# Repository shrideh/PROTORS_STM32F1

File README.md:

# PROTORS_STM32F1
This is a repository of our **open-source board** based on the *STM32F103C8 microcontroller from STMicroelectronics*.

## Pinout and dimensions
For the available functions of every pin, we strongly encourage you to read the [microcontroller datasheet](https://www.st.com/resource/en/datasheet/stm32f103c8.pdf), or use `variant/variant.h` and `variant/PeripherialPins.c` files.

## Electronics
* Whole *KiCad project* is available in `PROTORS_STM32F1` folder.

## Requirements
[Arduino](https://www.arduino.cc/)<br>
[Arduino_Core_STM32](https://github.com/stm32duino/Arduino_Core_STM32)<br>

This board is tested with
**Arduino IDE 1.8.12** and **Arduino_Core_STM32 1.8.0**.

## Installation & Usage
To use this board within [Arduino IDE](https://www.arduino.cc/en/main/software) you need [STM32 core support for Arduino](https://github.com/stm32duino/Arduino_Core_STM32). Every new board is called *variant*, to add this variant to list, you first need to find out where are source files on your system (follow [Where are sources](https://github.com/stm32duino/wiki/wiki/Where-are-sources#stm32-core-sources-files-location) page).

* Create folder `PROTORS_STM32F1` in `variants` folder and copy all files from this repositories `variant` folder (`ldscript.ld`, `PeripheralPins.c`, `PinNamesVar.h`, `variant.cpp`, and `variant.h`).
* Append `boards_additional.txt` content to `boards.txt` file (it is in same folder as `variant` folder), to declare the new variant.
* Restart *Arduino IDE* and try your new board. From ***Tools/Board*** menu select `Generic STM32F1 series` then from ***Tools/Board part number*** select `PROTORS STM32F1`. Set all of the rest options and upload sketch using ***STM32CubeProgrammer (SWD)*** (ST-LINK/V2 programmer).
* It is possible to customize some core definitions or compiler options by adding a file named `build_opt.h` in the sketch directory (follow [Build options](https://github.com/stm32duino/wiki/wiki/Customize-build-options-using-build_opt.h) page)

## License
Copyright (C) 2020 PROTORS  <info@protors.co>

Licensed under CERN-OHL-P version 2

You may redistribute and modify this documentation and make products
using it under the terms of the [CERN-OHL-P v2](https://ohwr.org/project/cernohl/wikis/Documents/CERN-OHL-version-2).
This documentation is distributed WITHOUT ANY EXPRESS OR IMPLIED
WARRANTY, INCLUDING OF MERCHANTABILITY, SATISFACTORY QUALITY
AND FITNESS FOR A PARTICULAR PURPOSE. Please see the CERN-OHL-P v2
for applicable conditions.

For more information view [LICENSE.txt](./LICENSE.txt) file.

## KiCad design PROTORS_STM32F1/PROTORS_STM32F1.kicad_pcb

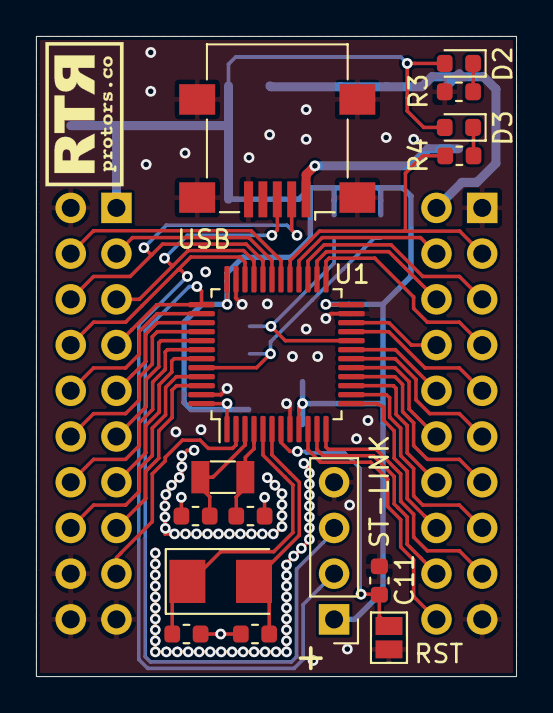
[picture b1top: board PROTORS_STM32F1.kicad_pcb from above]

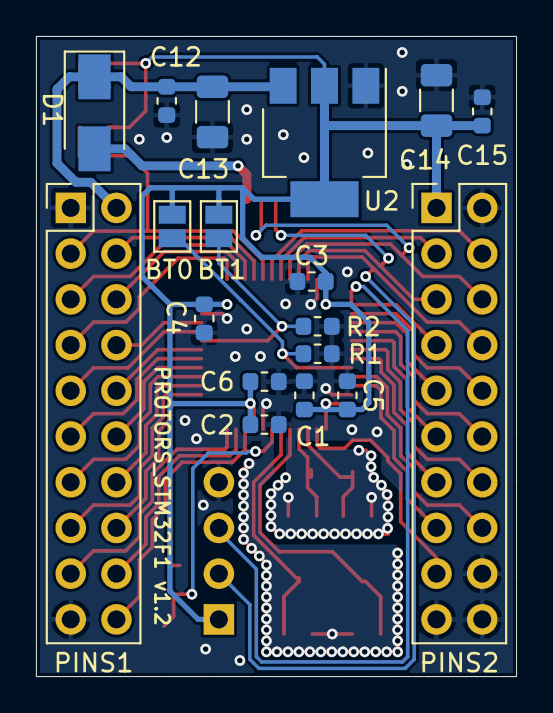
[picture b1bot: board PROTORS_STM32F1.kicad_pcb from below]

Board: 2 copper layers, 26.7 x 35.6 mm, 33 parts (18 on the bottom side), 45 nets.

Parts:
BT0: BOOT0; SolderJumper-2_P1.3mm_Open_Pad1.0x1.5mm
BT1: BOOT1; SolderJumper-2_P1.3mm_Open_Pad1.0x1.5mm
C1: 4.7uF; C_0603_1608Metric
C2: 1uF; C_0603_1608Metric
C3, C4, C5, C11, C12, C15: 100nF; C_0603_1608Metric
C6: 10nF; C_0603_1608Metric
C7, C8: 20pF; C_0603_1608Metric
C9, C10: 12pF; C_0603_1608Metric
C13, C14: 10uF; C_1206_3216Metric
D1: SS14; D_SMA
D2, D3: LED; LED_0603_1608Metric
PINS1: PINS_1; PinHeader_2x10_P2.54mm_Vertical
PINS2: PINS_2; PinHeader_2x10_P2.54mm_Vertical
R1, R2: 10k; R_0603_1608Metric
R3, R4: 1k; R_0603_1608Metric
RST: RESET; SolderJumper-2_P1.3mm_Open_Pad1.0x1.5mm
ST-LINK: ST-LINK; PinHeader_1x04_P2.54mm_Vertical
U1: STM32F103C8Tx; LQFP-48_7x7mm_P0.5mm
U2: AMS1117-3.3; SOT-223-3_TabPin2
USB: USB_B_Mini; USB_Mini-B_Lumberg_2486_01_Horizontal
Y1: 8MHz; Crystal_SMD_5032-2Pin_5.0x3.2mm
Y2: 32.768kHz; Crystal_SMD_3215-2Pin_3.2x1.5mm

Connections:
+3V3: BT0.2, BT1.2, C1.2, C2.2, C3.2, C4.2, C5.2, C6.2, C14.1, C15.1, D2.2, D3.2, PINS2.1, ST-LINK.1, U1.1, U1.9, U1.24, U1.36, U1.48, U2.2
+5V: C12.2, C13.1, D1.1, PINS1.2, U2.3
BOOT_0: BT0.1, R1.1, U1.44
GND: C1.1, C2.1, C3.1, C4.1, C5.1, C6.1, C7.2, C8.2, C9.2, C10.2, C11.1, C12.1, C13.2, C14.2, C15.2, PINS1.1, PINS1.19, PINS2.2, PINS2.18, PINS2.19, PINS2.20, R1.2, R2.2, R3.1, RST.2, ST-LINK.4, U1.8, U1.23, U1.35, U1.47, U2.1, USB.5, USB.6
HSE_1: C7.1, U1.5, Y1.1
HSE_2: C8.1, U1.6, Y1.2
LSE_1: C9.1, U1.3, Y2.1
LSE_2: C10.1, U1.4, Y2.2
unnamed: D1.2, USB.1
unnamed: D2.1, R3.2
unnamed: D3.1, R4.2
PA_0: PINS1.20, U1.10
PA_1: PINS1.18, U1.11
PA_2: PINS1.17, U1.12
PA_3: PINS1.16, U1.13
PA_4: PINS1.15, U1.14
PA_5: PINS1.14, U1.15
PA_6: PINS1.13, U1.16
PA_7: PINS1.12, U1.17
PA_8: PINS1.3, R4.1, U1.29
PA_9: PINS2.4, U1.30
PA_10: PINS2.3, U1.31
PA_11: PINS2.6, U1.32, USB.2
PA_12: PINS2.5, U1.33, USB.3
PA_13: PINS2.8, ST-LINK.2, U1.34
PA_14: PINS2.7, ST-LINK.3, U1.37
PA_15: PINS2.10, U1.38
PB_0: PINS1.11, U1.18
PB_1: PINS1.10, U1.19
PB_2: BT1.1, R2.1, U1.20
PB_3: PINS2.9, U1.39
PB_4: PINS2.12, U1.40
PB_5: PINS2.11, U1.41
PB_6: PINS2.14, U1.42
PB_7: PINS2.13, U1.43
PB_8: PINS2.16, U1.45
PB_9: PINS2.15, U1.46
PB_10: PINS1.9, U1.21
PB_11: PINS1.8, U1.22
PB_12: PINS1.7, U1.25
PB_13: PINS1.6, U1.26
PB_14: PINS1.5, U1.27
PB_15: PINS1.4, U1.28
PC_13: PINS2.17, U1.2
RST: C11.2, RST.1, U1.7

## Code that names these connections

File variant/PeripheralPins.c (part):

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
#ifdef HAL_ADC_MODULE_ENABLED
WEAK const PinMap PinMap_ADC[] = {
  {PA_0,  ADC1,  STM_PIN_DATA_EXT(STM_MODE_ANALOG, GPIO_NOPULL, 0, 0, 0)}, // ADC1_IN0
  //  {PA_0,  ADC2,  STM_PIN_DATA_EXT(STM_MODE_ANALOG, GPIO_NOPULL, 0, 0, 0)}, // ADC2_IN0
  {PA_1,  ADC1,  STM_PIN_DATA_EXT(STM_MODE_ANALOG, GPIO_NOPULL, 0, 1, 0)}, // ADC1_IN1
  //  {PA_1,  ADC2,  STM_PIN_DATA_EXT(STM_MODE_ANALOG, GPIO_NOPULL, 0, 1, 0)}, // ADC2_IN1
  {PA_2,  ADC1,  STM_PIN_DATA_EXT(STM_MODE_ANALOG, GPIO_NOPULL, 0, 2, 0)}, // ADC1_IN2
  //  {PA_2,  ADC2,  STM_PIN_DATA_EXT(STM_MODE_ANALOG, GPIO_NOPULL, 0, 2, 0)}, // ADC2_IN2
  {PA_3,  ADC1,  STM_PIN_DATA_EXT(STM_MODE_ANALOG, GPIO_NOPULL, 0, 3, 0)}, // ADC1_IN3
  //  {PA_3,  ADC2,  STM_PIN_DATA_EXT(STM_MODE_ANALOG, GPIO_NOPULL, 0, 3, 0)}, // ADC2_IN3
  {PA_4,  ADC1,  STM_PIN_DATA_EXT(STM_MODE_ANALOG, GPIO_NOPULL, 0, 4, 0)}, // ADC1_IN4
  //  {PA_4,  ADC2,  STM_PIN_DATA_EXT(STM_MODE_ANALOG, GPIO_NOPULL, 0, 4, 0)}, // ADC2_IN4
  {PA_5,  ADC1,  STM_PIN_DATA_EXT(STM_MODE_ANALOG, GPIO_NOPULL, 0, 5, 0)}, // ADC1_IN5
  //  {PA_5,  ADC2,  STM_PIN_DATA_EXT(STM_MODE_ANALOG, GPIO_NOPULL, 0, 5, 0)}, // ADC2_IN5
  {PA_6,  ADC1,  STM_PIN_DATA_EXT(STM_MODE_ANALOG, GPIO_NOPULL, 0, 6, 0)}, // ADC1_IN6
  //  {PA_6,  ADC2,  STM_PIN_DATA_EXT(STM_MODE_ANALOG, GPIO_NOPULL, 0, 6, 0)}, // ADC2_IN6
  {PA_7,  ADC1,  STM_PIN_DATA_EXT(STM_MODE_ANALOG, GPIO_NOPULL, 0, 7, 0)}, // ADC1_IN7
  //  {PA_7,  ADC2,  STM_PIN_DATA_EXT(STM_MODE_ANALOG, GPIO_NOPULL, 0, 7, 0)}, // ADC2_IN7
  {PB_0,  ADC1,  STM_PIN_DATA_EXT(STM_MODE_ANALOG, GPIO_NOPULL, 0, 8, 0)}, // ADC1_IN8
  //  {PB_0,  ADC2,  STM_PIN_DATA_EXT(STM_MODE_ANALOG, GPIO_NOPULL, 0, 8, 0)}, // ADC2_IN8
  {PB_1,  ADC1,  STM_PIN_DATA_EXT(STM_MODE_ANALOG, GPIO_NOPULL, 0, 9, 0)}, // ADC1_IN9
  //  {PB_1,  ADC2,  STM_PIN_DATA_EXT(STM_MODE_ANALOG, GPIO_NOPULL, 0, 9, 0)}, // ADC2_IN9
  {NC,    NP,    0}
};
#endif
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
#ifdef HAL_I2C_MODULE_ENABLED
WEAK const PinMap PinMap_I2C_SDA[] = {
  {PB_7,  I2C1, STM_PIN_DATA(STM_MODE_AF_OD, GPIO_NOPULL, AFIO_NONE)},
  {PB_9,  I2C1, STM_PIN_DATA(STM_MODE_AF_OD, GPIO_NOPULL, AFIO_I2C1_ENABLE)},
#ifndef ARDUINO_BLUEPILL_F103C6
  {PB_11, I2C2, STM_PIN_DATA(STM_MODE_AF_OD, GPIO_NOPULL, AFIO_NONE)},
#endif
  {NC,    NP,    0}
};
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
#ifdef HAL_I2C_MODULE_ENABLED
WEAK const PinMap PinMap_I2C_SCL[] = {
  {PB_6,  I2C1, STM_PIN_DATA(STM_MODE_AF_OD, GPIO_NOPULL, AFIO_NONE)},
  {PB_8,  I2C1, STM_PIN_DATA(STM_MODE_AF_OD, GPIO_NOPULL, AFIO_I2C1_ENABLE)},
#ifndef ARDUINO_BLUEPILL_F103C6
  {PB_10, I2C2, STM_PIN_DATA(STM_MODE_AF_OD, GPIO_NOPULL, AFIO_NONE)},
#endif
  {NC,    NP,    0}
};
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
#ifdef HAL_TIM_MODULE_ENABLED
WEAK const PinMap PinMap_PWM[] = {
  {PA_0,  TIM2,   STM_PIN_DATA_EXT(STM_MODE_AF_PP, GPIO_PULLUP, AFIO_NONE, 1, 0)}, // TIM2_CH1
  //  {PA_0,  TIM2,   STM_PIN_DATA_EXT(STM_MODE_AF_PP, GPIO_PULLUP, AFIO_TIM2_PARTIAL_2, 1, 0)}, // TIM2_CH1
  {PA_1,  TIM2,   STM_PIN_DATA_EXT(STM_MODE_AF_PP, GPIO_PULLUP, AFIO_NONE, 2, 0)}, // TIM2_CH2
  //  {PA_1,  TIM2,   STM_PIN_DATA_EXT(STM_MODE_AF_PP, GPIO_PULLUP, AFIO_TIM2_PARTIAL_2, 2, 0)}, // TIM2_CH2
  {PA_2,  TIM2,   STM_PIN_DATA_EXT(STM_MODE_AF_PP, GPIO_PULLUP, AFIO_NONE, 3, 0)}, // TIM2_CH3
  //  {PA_2,  TIM2,   STM_PIN_DATA_EXT(STM_MODE_AF_PP, GPIO_PULLUP, AFIO_TIM2_PARTIAL_1, 3, 0)}, // TIM2_CH3
  {PA_3,  TIM2,   STM_PIN_DATA_EXT(STM_MODE_AF_PP, GPIO_PULLUP, AFIO_NONE, 4, 0)}, // TIM2_CH4
  //  {PA_3,  TIM2,   STM_PIN_DATA_EXT(STM_MODE_AF_PP, GPIO_PULLUP, AFIO_TIM2_PARTIAL_1, 4, 0)}, // TIM2_CH4
  {PA_6,  TIM3,   STM_PIN_DATA_EXT(STM_MODE_AF_PP, GPIO_PULLUP, AFIO_NONE, 1, 0)}, // TIM3_CH1
  //  {PA_7,  TIM1,   STM_PIN_DATA_EXT(STM_MODE_AF_PP, GPIO_PULLUP, AFIO_TIM1_PARTIAL, 1, 1)}, // TIM1_CH1N
  {PA_7,  TIM3,   STM_PIN_DATA_EXT(STM_MODE_AF_PP, GPIO_PULLUP, AFIO_NONE, 2, 0)}, // TIM3_CH2
  {PA_8,  TIM1,   STM_PIN_DATA_EXT(STM_MODE_AF_PP, GPIO_PULLUP, AFIO_NONE, 1, 0)}, // TIM1_CH1
  //  {PA_8,  TIM1,   STM_PIN_DATA_EXT(STM_MODE_AF_PP, GPIO_PULLUP, AFIO_TIM1_PARTIAL, 1, 0)}, // TIM1_CH1
  {PA_9,  TIM1,   STM_PIN_DATA_EXT(STM_MODE_AF_PP, GPIO_PULLUP, AFIO_NONE, 2, 0)}, // TIM1_CH2
  //  {PA_9,  TIM1,   STM_PIN_DATA_EXT(STM_MODE_AF_PP, GPIO_PULLUP, AFIO_TIM1_PARTIAL, 2, 0)}, // TIM1_CH2
  {PA_10, TIM1,   STM_PIN_DATA_EXT(STM_MODE_AF_PP, GPIO_PULLUP, AFIO_NONE, 3, 0)}, // TIM1_CH3
  //  {PA_10, TIM1,   STM_PIN_DATA_EXT(STM_MODE_AF_PP, GPIO_PULLUP, AFIO_TIM1_PARTIAL, 3, 0)}, // TIM1_CH3
  {PA_11, TIM1,   STM_PIN_DATA_EXT(STM_MODE_AF_PP, GPIO_PULLUP, AFIO_NONE, 4, 0)}, // TIM1_CH4
  //  {PA_11, TIM1,   STM_PIN_DATA_EXT(STM_MODE_AF_PP, GPIO_PULLUP, AFIO_TIM1_PARTIAL, 4, 0)}, // TIM1_CH4
  //  {PA_15, TIM2,   STM_PIN_DATA_EXT(STM_MODE_AF_PP, GPIO_PULLUP, AFIO_TIM2_PARTIAL_1, 1, 0)}, // TIM2_CH1
  {PA_15, TIM2,   STM_PIN_DATA_EXT(STM_MODE_AF_PP, GPIO_PULLUP, AFIO_TIM2_ENABLE, 1, 0)}, // TIM2_CH1
  //  {PB_0,  TIM1,   STM_PIN_DATA_EXT(STM_MODE_AF_PP, GPIO_PULLUP, AFIO_TIM1_PARTIAL, 2, 1)}, // TIM1_CH2N
  {PB_0,  TIM3,   STM_PIN_DATA_EXT(STM_MODE_AF_PP, GPIO_PULLUP, AFIO_NONE, 3, 0)}, // TIM3_CH3
  //  {PB_0,  TIM3,   STM_PIN_DATA_EXT(STM_MODE_AF_PP, GPIO_PULLUP, AFIO_TIM3_PARTIAL, 3, 0)}, // TIM3_CH3
  //  {PB_1,  TIM1,   STM_PIN_DATA_EXT(STM_MODE_AF_PP, GPIO_PULLUP, AFIO_TIM1_PARTIAL, 3, 1)}, // TIM1_CH3N
  {PB_1,  TIM3,   STM_PIN_DATA_EXT(STM_MODE_AF_PP, GPIO_PULLUP, AFIO_NONE, 4, 0)}, // TIM3_CH4
  //  {PB_1,  TIM3,   STM_PIN_DATA_EXT(STM_MODE_AF_PP, GPIO_PULLUP, AFIO_TIM3_PARTIAL, 4, 0)}, // TIM3_CH4
  //  {PB_3,  TIM2,   STM_PIN_DATA_EXT(STM_MODE_AF_PP, GPIO_PULLUP, AFIO_TIM2_PARTIAL_1, 2, 0)}, // TIM2_CH2
  {PB_3,  TIM2,   STM_PIN_DATA_EXT(STM_MODE_AF_PP, GPIO_PULLUP, AFIO_TIM2_ENABLE, 2, 0)}, // TIM2_CH2
  {PB_4,  TIM3,   STM_PIN_DATA_EXT(STM_MODE_AF_PP, GPIO_PULLUP, AFIO_TIM3_PARTIAL, 1, 0)}, // TIM3_CH1
  {PB_5,  TIM3,   STM_PIN_DATA_EXT(STM_MODE_AF_PP, GPIO_PULLUP, AFIO_TIM3_PARTIAL, 2, 0)}, // TIM3_CH2
#ifndef ARDUINO_BLUEPILL_F103C6
  {PB_6,  TIM4,   STM_PIN_DATA_EXT(STM_MODE_AF_PP, GPIO_PULLUP, AFIO_NONE, 1, 0)}, // TIM4_CH1
  {PB_7,  TIM4,   STM_PIN_DATA_EXT(STM_MODE_AF_PP, GPIO_PULLUP, AFIO_NONE, 2, 0)}, // TIM4_CH2
  {PB_8,  TIM4,   STM_PIN_DATA_EXT(STM_MODE_AF_PP, GPIO_PULLUP, AFIO_NONE, 3, 0)}, // TIM4_CH3
  {PB_9,  TIM4,   STM_PIN_DATA_EXT(STM_MODE_AF_PP, GPIO_PULLUP, AFIO_NONE, 4, 0)}, // TIM4_CH4
#endif
  //  {PB_10, TIM2,   STM_PIN_DATA_EXT(STM_MODE_AF_PP, GPIO_PULLUP, AFIO_TIM2_PARTIAL_2, 3, 0)}, // TIM2_CH3
  {PB_10, TIM2,   STM_PIN_DATA_EXT(STM_MODE_AF_PP, GPIO_PULLUP, AFIO_TIM2_ENABLE, 3, 0)}, // TIM2_CH3
  //  {PB_11, TIM2,   STM_PIN_DATA_EXT(STM_MODE_AF_PP, GPIO_PULLUP, AFIO_TIM2_PARTIAL_2, 4, 0)}, // TIM2_CH4
  {PB_11, TIM2,   STM_PIN_DATA_EXT(STM_MODE_AF_PP, GPIO_PULLUP, AFIO_TIM2_ENABLE, 4, 0)}, // TIM2_CH4
  {PB_13, TIM1,   STM_PIN_DATA_EXT(STM_MODE_AF_PP, GPIO_PULLUP, AFIO_NONE, 1, 1)}, // TIM1_CH1N
  {PB_14, TIM1,   STM_PIN_DATA_EXT(STM_MODE_AF_PP, GPIO_PULLUP, AFIO_NONE, 2, 1)}, // TIM1_CH2N
  {PB_15, TIM1,   STM_PIN_DATA_EXT(STM_MODE_AF_PP, GPIO_PULLUP, AFIO_NONE, 3, 1)}, // TIM1_CH3N
  {NC,    NP,    0}
};
#endif
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
#ifdef HAL_UART_MODULE_ENABLED
WEAK const PinMap PinMap_UART_TX[] = {
  {PA_2,  USART2,  STM_PIN_DATA(STM_MODE_AF_PP, GPIO_PULLUP, AFIO_NONE)},
  {PA_9,  USART1,  STM_PIN_DATA(STM_MODE_AF_PP, GPIO_PULLUP, AFIO_NONE)},
  //{PB_6,  USART1,  STM_PIN_DATA(STM_MODE_AF_PP, GPIO_PULLUP, AFIO_USART1_ENABLE)},
#ifndef ARDUINO_BLUEPILL_F103C6
  {PB_10, USART3,  STM_PIN_DATA(STM_MODE_AF_PP, GPIO_PULLUP, AFIO_NONE)},
#endif
  {NC,    NP,    0}
};
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
#ifdef HAL_UART_MODULE_ENABLED
WEAK const PinMap PinMap_UART_RX[] = {
  {PA_3,  USART2,  STM_PIN_DATA(STM_MODE_INPUT, GPIO_PULLUP, AFIO_NONE)},
  {PA_10, USART1,  STM_PIN_DATA(STM_MODE_INPUT, GPIO_PULLUP, AFIO_NONE)},
  //{PB_7,  USART1,  STM_PIN_DATA(STM_MODE_INPUT, GPIO_PULLUP, AFIO_USART1_ENABLE)},
#ifndef ARDUINO_BLUEPILL_F103C6
  {PB_11, USART3,  STM_PIN_DATA(STM_MODE_INPUT, GPIO_PULLUP, AFIO_NONE)},
#endif
  {NC,    NP,    0}
};
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
#ifdef HAL_UART_MODULE_ENABLED
WEAK const PinMap PinMap_UART_RTS[] = {
  {PA_1,  USART2,  STM_PIN_DATA(STM_MODE_AF_PP, GPIO_PULLUP, AFIO_NONE)},
  {PA_12, USART1,  STM_PIN_DATA(STM_MODE_AF_PP, GPIO_PULLUP, AFIO_NONE)},
#ifndef ARDUINO_BLUEPILL_F103C6
  {PB_14, USART3,  STM_PIN_DATA(STM_MODE_AF_PP, GPIO_PULLUP, AFIO_NONE)},
  //  {PB_14, USART3,  STM_PIN_DATA(STM_MODE_AF_PP, GPIO_PULLUP, AFIO_USART3_PARTIAL)},
#endif
  {NC,    NP,    0}
};
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
#ifdef HAL_UART_MODULE_ENABLED
WEAK const PinMap PinMap_UART_CTS[] = {
  {PA_0,  USART2,  STM_PIN_DATA(STM_MODE_AF_PP, GPIO_PULLUP, AFIO_NONE)},
  {PA_11, USART1,  STM_PIN_DATA(STM_MODE_AF_PP, GPIO_PULLUP, AFIO_NONE)},
#ifndef ARDUINO_BLUEPILL_F103C6
  {PB_13, USART3,  STM_PIN_DATA(STM_MODE_AF_PP, GPIO_PULLUP, AFIO_NONE)},
  //  {PB_13, USART3,  STM_PIN_DATA(STM_MODE_AF_PP, GPIO_PULLUP, AFIO_USART3_PARTIAL)},
#endif
  {NC,    NP,    0}
};
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
#ifdef HAL_SPI_MODULE_ENABLED
WEAK const PinMap PinMap_SPI_MOSI[] = {
  {PA_7,  SPI1, STM_PIN_DATA(STM_MODE_AF_PP, GPIO_PULLUP, AFIO_NONE)},
  {PB_5,  SPI1, STM_PIN_DATA(STM_MODE_AF_PP, GPIO_PULLUP, AFIO_SPI1_ENABLE)},
#ifndef ARDUINO_BLUEPILL_F103C6
  {PB_15, SPI2, STM_PIN_DATA(STM_MODE_AF_PP, GPIO_PULLUP, AFIO_NONE)},
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
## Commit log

2020-05-08 Update board

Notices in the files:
variant/PeripheralPins.c:
Copyright (c) 2019, STMicroelectronics
All rights reserved.
